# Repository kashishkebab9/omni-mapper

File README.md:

# omni-mapper

Omni-Wheeled Robot with custom PCB
All Mechanical Assemblies, PCBs, Firmware, and Software designed, architected and programmed by Kashish Garg

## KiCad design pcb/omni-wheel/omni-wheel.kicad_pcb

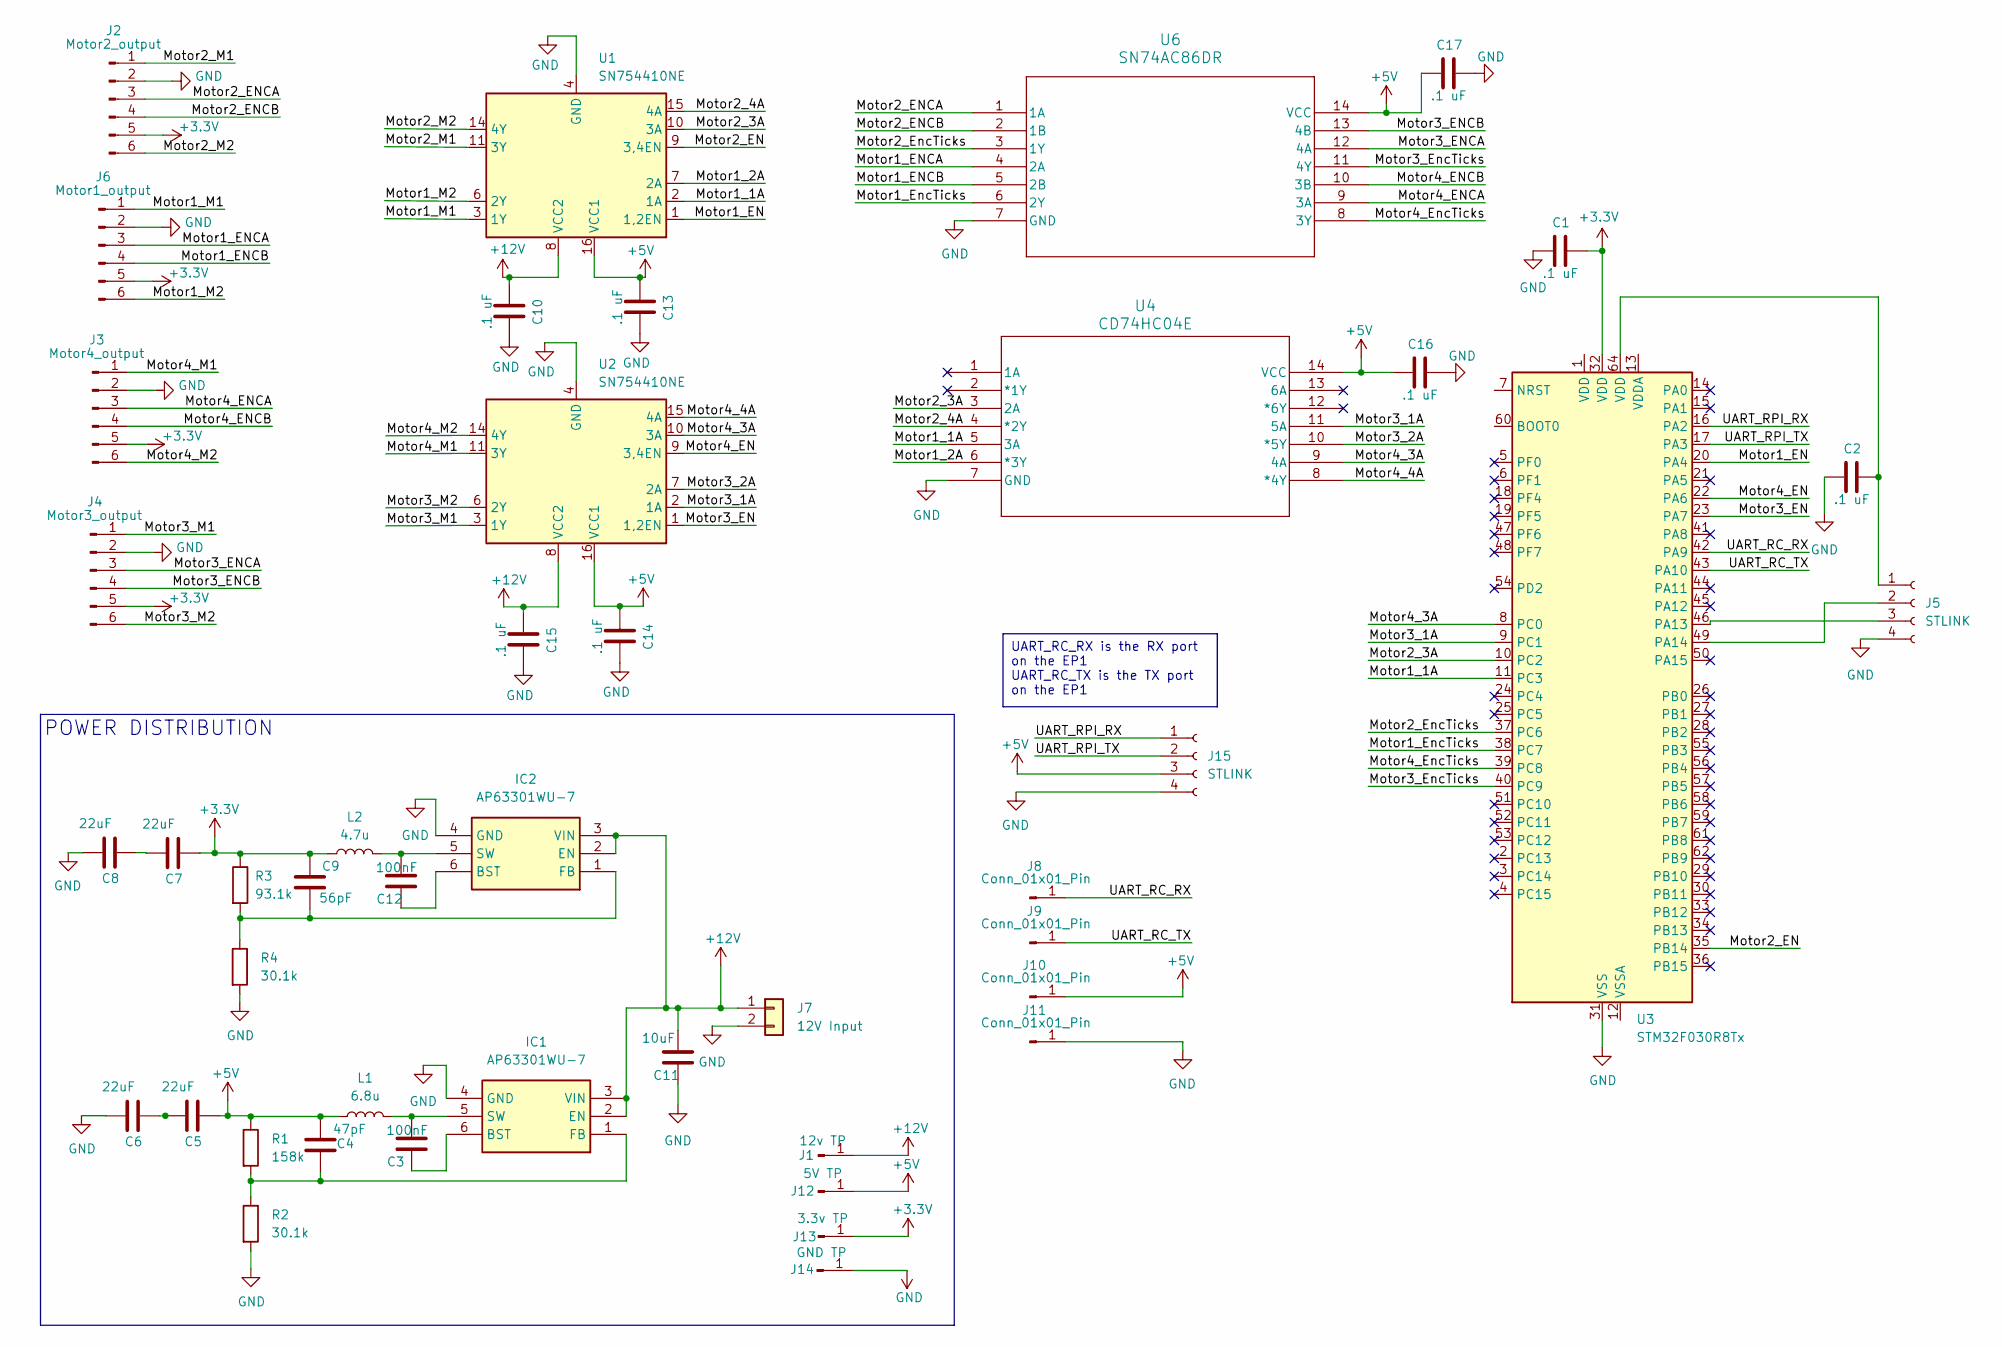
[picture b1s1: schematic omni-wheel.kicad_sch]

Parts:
C1, C2, C10, C13, C14, C15, C16, C17: .1 uF; C_0603_1608Metric; digikey# 311-1088-2-ND
C3, C12: 100nF; C_0603_1608Metric; digikey# 311-1088-2-ND
C4: 47pF; C_0603_1608Metric; digikey# 1276-1037-2-ND
C5, C6, C7, C8: 22uF; C_0603_1608Metric; digikey# 1276-1274-2-ND
C9: 56pF; C_0603_1608Metric; digikey# 1276-1197-2-ND
C11: 10uF; C_0603_1608Metric; digikey# 1276-1119-2-ND
IC1, IC2: AP63301WU-7; SOT95P280X100-6N; Manufacturer_Part_Number AP63301WU-7; digikey# 31-AP63301WU-7TR-ND
J1: 12v TP; TestPoint_THTPad_1.0x1.0mm_Drill0.5mm
J2: Motor2_output; JST_PH_B6B-PH-K_1x06_P2.00mm_Vertical
J3: Motor4_output; JST_PH_B6B-PH-K_1x06_P2.00mm_Vertical
J4: Motor3_output; JST_PH_B6B-PH-K_1x06_P2.00mm_Vertical
J5, J15: STLINK; PinHeader_1x04_P2.54mm_Vertical
J6: Motor1_output; JST_PH_B6B-PH-K_1x06_P2.00mm_Vertical
J7: 12V Input; AMASS_XT60PW-M_1x02_P7.20mm_Horizontal
J8, J9, J10, J11: Conn_01x01_Pin; TestPoint_THTPad_2.0x2.0mm_Drill1.0mm
J12: 5V TP; TestPoint_THTPad_1.0x1.0mm_Drill0.5mm
J13: 3.3v TP; TestPoint_THTPad_1.0x1.0mm_Drill0.5mm
J14: GND TP; TestPoint_THTPad_1.0x1.0mm_Drill0.5mm
L1: 6.8u; L_0603_1608Metric; digikey# 535-11606-2-ND
L2: 4.7u; L_0603_1608Metric; digikey# 535-11602-2-ND
R1: 158k; R_0603_1608Metric; digikey# 541-158KHTR-ND
R2, R4: 30.1k; R_0603_1608Metric; digikey# 311-30.1KHRTR-ND
R3: 93.1k; R_0603_1608Metric
U1, U2: SN754410NE; DIP-16_W7.62mm
U3: STM32F030R8Tx; LQFP-64_10x10mm_P0.5mm
U4: CD74HC04E; N14
U6: SN74AC86DR; D14

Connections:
+3.3V: C1.2, C7.2, C9.1, J2.5, J3.5, J4.5, J6.5, J13.1, L2.1, R3.1, U3.32 (VDD)
+5V: C4.1, C5.2, C13.1, C14.1, C16.1, C17.1, J10.1, J12.1, J15.3, L1.1, R1.1, U1.16 (VCC1), U2.16 (VCC1), U4.14 (VCC), U6.14 (VCC)
/Motor1_1A: U1.2 (1A), U3.11 (PC3), U4.5 (3A)
/Motor1_2A: U1.7 (2A), U4.6 (*3Y)
/Motor1_EN: U1.1 (1,2EN), U3.20 (PA4)
/Motor1_ENCA: J6.3, U6.4 (2A)
/Motor1_ENCB: J6.4, U6.5 (2B)
/Motor1_EncTicks: U3.38 (PC7), U6.6 (2Y)
/Motor1_M1: J6.1, U1.3 (1Y)
/Motor1_M2: J6.6, U1.6 (2Y)
/Motor2_3A: U1.10 (3A), U3.10 (PC2), U4.3 (2A)
/Motor2_4A: U1.15 (4A), U4.4 (*2Y)
/Motor2_EN: U1.9 (3,4EN), U3.35 (PB14)
/Motor2_ENCA: J2.3, U6.1 (1A)
/Motor2_ENCB: J2.4, U6.2 (1B)
/Motor2_EncTicks: U3.37 (PC6), U6.3 (1Y)
/Motor2_M1: J2.1, U1.11 (3Y)
/Motor2_M2: J2.6, U1.14 (4Y)
/Motor3_1A: U2.2 (1A), U3.9 (PC1), U4.11 (5A)
/Motor3_2A: U2.7 (2A), U4.10 (*5Y)
/Motor3_EN: U2.1 (1,2EN), U3.23 (PA7)
/Motor3_ENCA: J4.3, U6.12 (4A)
/Motor3_ENCB: J4.4, U6.13 (4B)
/Motor3_EncTicks: U3.40 (PC9), U6.11 (4Y)
/Motor3_M1: J4.1, U2.3 (1Y)
/Motor3_M2: J4.6, U2.6 (2Y)
/Motor4_3A: U2.10 (3A), U3.8 (PC0), U4.9 (4A)
/Motor4_4A: U2.15 (4A), U4.8 (*4Y)
/Motor4_EN: U2.9 (3,4EN), U3.22 (PA6)
/Motor4_ENCA: J3.3, U6.9 (3A)
/Motor4_ENCB: J3.4, U6.10 (3B)
/Motor4_EncTicks: U3.39 (PC8), U6.8 (3Y)
/Motor4_M1: J3.1, U2.11 (3Y)
/Motor4_M2: J3.6, U2.14 (4Y)
/UART_RC_RX: J8.1, U3.42 (PA9)
/UART_RC_TX: J9.1, U3.43 (PA10)
/UART_RPI_RX: J15.1, U3.16 (PA2)
/UART_RPI_TX: J15.2, U3.17 (PA3)
GND: C1.1, C2.1, C6.1, C8.1, C10.2, C11.2, C13.2, C14.2, C15.2, C16.2, C17.2, IC1.4 (GND), IC2.4 (GND), J2.2, J3.2, J4.2, J5.4, J6.2, J7.2, J11.1, J14.1, J15.4, R2.2, R4.2, U1.4 (GND), U1.5 (GND), U1.12 (GND), U1.13 (GND), U2.4 (GND), U2.5 (GND), U2.12 (GND), U2.13 (GND), U3.31 (VSS), U3.63 (VSS), U4.7 (GND), U6.7 (GND)
unnamed: C5.1, C6.2
unnamed: C7.1, C8.2
unnamed: C3.2, IC1.6 (BST)
unnamed: C4.2, IC1.1 (FB), R1.2, R2.1
unnamed: C3.1, IC1.5 (SW), L1.2
unnamed: C12.2, IC2.6 (BST)
unnamed: C9.2, IC2.1 (FB), R3.2, R4.1
unnamed: C12.1, IC2.5 (SW), L2.2
unnamed: C2.2, J5.1, U3.64 (VDD)
unnamed: J5.2, U3.49 (PA14)
unnamed: J5.3, U3.46 (PA13)

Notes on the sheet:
UART_RC_RX is the RX port on the EP1 UART_RC_TX is the TX port on the EP1
POWER DISTRIBUTION

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
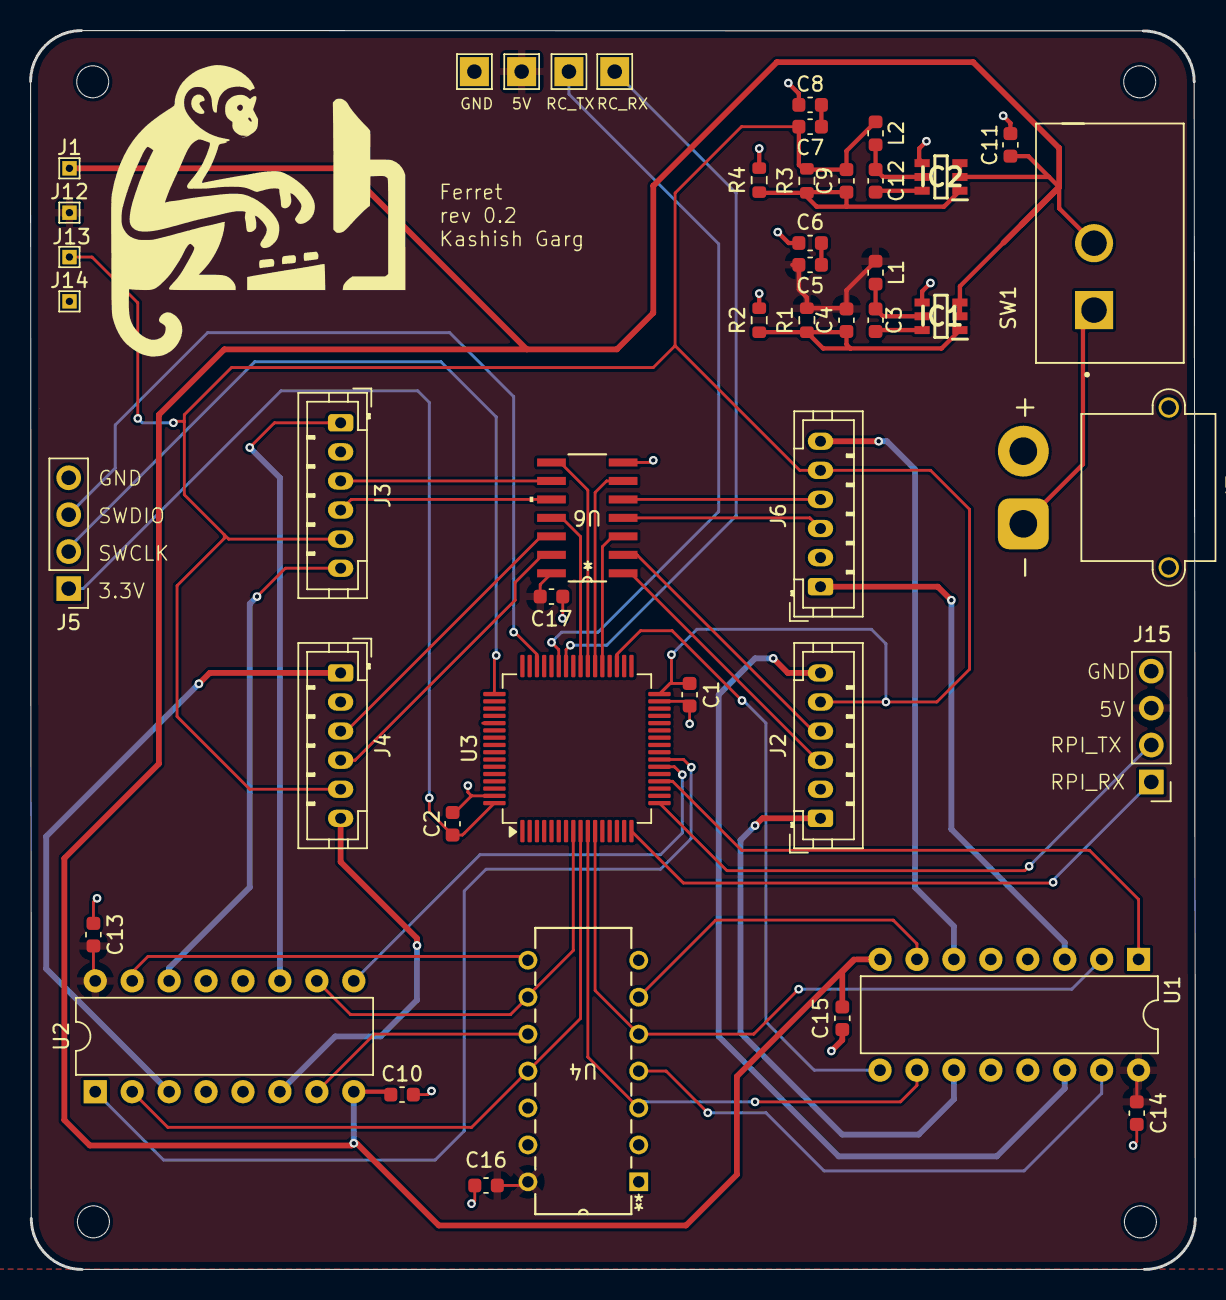
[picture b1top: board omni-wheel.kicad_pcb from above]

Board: 2 copper layers, 80.1 x 85.2 mm, 46 parts (0 on the bottom side), 52 nets.

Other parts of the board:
SW1: SW_SPST; SW_GF-123-0054

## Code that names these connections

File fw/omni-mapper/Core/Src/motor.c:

/*
 * Copyright (c) 2024 Kashish Garg
 *
 * Permission is hereby granted, free of charge, to any person obtaining a copy
 * of this software and associated documentation files (the "Software"), to deal
 * in the Software without restriction, including without limitation the rights
 * to use, copy, modify, merge, publish, distribute, sublicense, and/or sell
 * copies of the Software, and to permit persons to whom the Software is
 * furnished to do so, subject to the following conditions:
 *
 * The above copyright notice and this permission notice shall be included in all
 * copies or substantial portions of the Software.
 *
 * THE SOFTWARE IS PROVIDED "AS IS", WITHOUT WARRANTY OF ANY KIND, EXPRESS OR
 * IMPLIED, INCLUDING BUT NOT LIMITED TO THE WARRANTIES OF MERCHANTABILITY,
 * FITNESS FOR A PARTICULAR PURPOSE AND NONINFRINGEMENT. IN NO EVENT SHALL THE
 * AUTHORS OR COPYRIGHT HOLDERS BE LIABLE FOR ANY CLAIM, DAMAGES OR OTHER
 * LIABILITY, WHETHER IN AN ACTION OF CONTRACT, TORT OR OTHERWISE, ARISING FROM,
 * OUT OF OR IN CONNECTION WITH THE SOFTWARE OR THE USE OR OTHER DEALINGS IN THE
 * SOFTWARE.
 */

#include "motor.h"
#include "timer.h"
#include "gpio.h"
#include "stm32f0xx_hal.h"
#include <stdint.h>

// We will be using the SN7544 Dual H-Bridge Motor Driver
// The four pins for PWM I am thinking are:
// PA4  (Pin 20) -> Time14_CH1 AF4 :: Motor 1 EN (3,4EN)
// PB14 (Pin 36) -> Time15_CH1 AF0 :: Motor 2 EN (1,2EN)
// PA6  (Pin 22) -> Time16_CH1 AF5 :: Motor 3 EN (1,2EN)
// PA7  (Pin 23) -> Time17_CH1 AF5 :: Motor 4 EN (3,4EN)


void SetupMotorPwm(GPIO_TypeDef * GPIOx, uint8_t pwm_pin, uint8_t af){
  
  // TODO: Check if TIMx is NULL   
  
  TIM_TypeDef * TIMx = SetupTimer(GPIOx, pwm_pin, af);

  // Settings for 0% duty cycle, change CCR1 for the duty cycle/speed required
  TIMx->CCR1 = 21;
  TIMx->PSC = 8000;
  TIMx->ARR = 20;

  // Set CCMR1 as Output
  TIMx->CCMR1 &~ (1 << 0); 
  TIMx->CCMR1 &~ (1 << 1); 

  // Active Polarity High
  TIMx->CCER |= (1 << 1);

  // PWM Mode
  TIMx->CCMR1 |= (1 << 6);
  TIMx->CCMR1 |= (1 << 5);
  TIMx->CCMR1 &~ (1 << 4);

  // Enable Compare Channel 1
  TIMx->CCER |= (1 << 0);

  // Initialize all Registers
  TIMx->EGR |= (1 << 0);

  // Enable output
  TIMx->BDTR |= (1 << 15);

  // 8MHZ / 8000 = 1000 cts/second
  TIMx->CR1 |= (1 << 0);

}

void SetupMotorDir(GPIO_TypeDef * GPIOx, uint8_t dir_pin){
  
  SetupGpioOut(GPIOx, dir_pin);

  // test:
  SetGpioOutOn(GPIOx, dir_pin);

}


void SetupMotor(MotorHandle motor_handle) {

  SetupMotorPwm(motor_handle.GPIOx_pwm, motor_handle.pwm_pin, motor_handle.pwm_af);
  SetupMotorDir(motor_handle.GPIOx_dir, motor_handle.dir_pin);
  SetupMotorEnc(motor_handle.GPIOx_enc, motor_handle.enc_pin);

}

void SetMotorDutyCycle(MotorHandle motor_handle, uint8_t pwm) {
  // Input a percentage (0- 100)
  // TODO: Set ErrorHandler if pwm is out of bounds
  
  TIM_TypeDef *TIMx = get_timer_from_pin(motor_handle.GPIOx_pwm, motor_handle.pwm_pin, motor_handle.pwm_af);

  if (pwm == 0) {
    TIMx->CCR1 = 21;

  } else {

    // x / 100 = y / 20
    // 20x = 100y
    // .2x = y

    pwm /= (int)pwm/5;
    TIMx->CCR1 = pwm;

  }
}

void SetupMotorEnc(GPIO_TypeDef * GPIOx, uint8_t enc_pin){
  
  SetupGpioIn(GPIOx, enc_pin);

}

void SetMotorDirection(){
}

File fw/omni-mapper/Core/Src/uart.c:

/*
 * Copyright (c) 2024 Kashish Garg
 *
 * Permission is hereby granted, free of charge, to any person obtaining a copy
 * of this software and associated documentation files (the "Software"), to deal
 * in the Software without restriction, including without limitation the rights
 * to use, copy, modify, merge, publish, distribute, sublicense, and/or sell
 * copies of the Software, and to permit persons to whom the Software is
 * furnished to do so, subject to the following conditions:
 *
 * The above copyright notice and this permission notice shall be included in all
 * copies or substantial portions of the Software.
 *
 * THE SOFTWARE IS PROVIDED "AS IS", WITHOUT WARRANTY OF ANY KIND, EXPRESS OR
 * IMPLIED, INCLUDING BUT NOT LIMITED TO THE WARRANTIES OF MERCHANTABILITY,
 * FITNESS FOR A PARTICULAR PURPOSE AND NONINFRINGEMENT. IN NO EVENT SHALL THE
 * AUTHORS OR COPYRIGHT HOLDERS BE LIABLE FOR ANY CLAIM, DAMAGES OR OTHER
 * LIABILITY, WHETHER IN AN ACTION OF CONTRACT, TORT OR OTHERWISE, ARISING FROM,
 * OUT OF OR IN CONNECTION WITH THE SOFTWARE OR THE USE OR OTHER DEALINGS IN THE
 * SOFTWARE.
 */

#include "uart.h"
#include <stdint.h>
#include <string.h>
#include <stdio.h>

// There are only two UART peripherals that we can use on this mcu
// No need to map things, we can just have two functions to set up each of these
// PA9  (Pin 42) -> USART1_TX AF1 :: RC RX
// PA10 (Pin 43) -> USART1_RX AF1 :: RC TX
// PA2  (Pin 16) -> USART2_TX AF1 :: RaspberryPi RX
// PA3  (Pin 17) -> USART2_RX AF1 :: RaspberryPi TX

USART_TypeDef* SetupUartRc() {

  // All ports get enabled in main()
  // RCC->AHBENR |= RCC_AHBENR_GPIOAEN;
  
  /* 
   * Enable the USART1 Peripheral in RCC
   * Page 114 of 
   * https://www.newbiehack.com/Documents/STM32F030Reference.pdf
  */ 
  RCC->APB2ENR |= (1 << 14);

  /* 
   * Alternate Pin Mode
   * Page 137 of 
   * https://www.newbiehack.com/Documents/STM32F030Reference.pdf
   * and Page 34 of 
   * https://www.st.com/content/ccc/resource/technical/document/datasheet/a4/5d/0b/0e/87/c4/4d/71/DM00088500.pdf/files/DM00088500.pdf/jcr:content/translations/en.DM00088500.pdf
  */ 
  GPIOA->MODER |= (1 << 21);
  GPIOA->MODER &~ (1 << 20);
  GPIOA->MODER |= (1 << 19);
  GPIOA->MODER &~ (1 << 18);

  /* 
   * Actual Alternate Function Number (AF1) for both Pin 9 and 10
   * Page 142 of 
   * https://www.newbiehack.com/Documents/STM32F030Reference.pdf
  */ 
  GPIOA->AFR[1] &~ (1 << 7);
  GPIOA->AFR[1] &~ (1 << 6);
  GPIOA->AFR[1] &~ (1 << 5);
  GPIOA->AFR[1] |= (1 << 4);

  GPIOA->AFR[1] &~ (1 << 11);
  GPIOA->AFR[1] &~ (1 << 10);
  GPIOA->AFR[1] &~ (1 << 9);
  GPIOA->AFR[1] |= (1 << 8);

  /* 
   * Program the M0 and M1 Bit in the USART CR1
   * 00 for 8 bit word length
   * Disable USART while we configure          
   * Page 623 of 
   * https://www.newbiehack.com/Documents/STM32F030Reference.pdf
  */ 

  USART1->CR1 = 0x00000000;
  USART1->CR1 &~ (1 << 12);
  USART1->CR1 &~ (1 << 28);
  USART1->CR1 &~ (1 << 0);

  /* 
   * BRR
   * Our Clock rate is 8MHz
   * We want to oversample by 16. Meaning the RX line will sample 16x more the baudrate
   *Baud = 115200
   * Clock = 8,000,000
   * USART_DIV = 8,000,000/115200
   * USART_DIV = 69.4 => 69
   * Page 631 of 
   * https://www.newbiehack.com/Documents/STM32F030Reference.pdf
  */ 

  uint32_t reg = USART1->BRR;
  reg |= 69;
  USART1->BRR = reg;

  /* 
   * Program the Number of Stop Bits in USART CR2
   * minicom uses 1 stop bit by default
   * Page 142 of 
   * https://www.newbiehack.com/Documents/STM32F030Reference.pdf
  */ 

  USART1->CR2 &~ (1 << 13);
  USART1->CR2 &~ (1 << 12);

  /* 
   * Enable the USART by writing the UE bit in USART_CR1 register to 1
   * minicom uses 1 stop bit by default
   * Page 623 of 
   * https://www.newbiehack.com/Documents/STM32F030Reference.pdf
  */ 
  USART1->CR1 |= (1<<0);

  return USART1;
}

USART_TypeDef* SetupUartRpi() {
  // All ports get enabled in main()
  // RCC->AHBENR |= RCC_AHBENR_GPIOAEN;
  
  /* 
   * Enable the USART1 Peripheral in RCC
   * Page 114 of 
   * https://www.newbiehack.com/Documents/STM32F030Reference.pdf
  */ 
  RCC->APB1ENR |= (1 << 17);

  /* 
   * Alternate Pin Mode
   * Page 137 of 
   * https://www.newbiehack.com/Documents/STM32F030Reference.pdf
   * and Page 34 of 
   * https://www.st.com/content/ccc/resource/technical/document/datasheet/a4/5d/0b/0e/87/c4/4d/71/DM00088500.pdf/files/DM00088500.pdf/jcr:content/translations/en.DM00088500.pdf
  */ 
  GPIOA->MODER |= (1 << 7);
  GPIOA->MODER &~ (1 << 6);
  GPIOA->MODER |= (1 << 5);
  GPIOA->MODER &~ (1 << 4);

  /* 
   * Actual Alternate Function Number (AF1) for both Pin 9 and 10
   * Page 142 of 
   * https://www.newbiehack.com/Documents/STM32F030Reference.pdf
  */ 
  GPIOA->AFR[0] &~ (1 << 11);
  GPIOA->AFR[0] &~ (1 << 10);
  GPIOA->AFR[0] &~ (1 << 9);
  GPIOA->AFR[0] |= (1 << 8);

  GPIOA->AFR[0] &~ (1 << 15);
  GPIOA->AFR[0] &~ (1 << 14);
  GPIOA->AFR[0] &~ (1 << 13);
  GPIOA->AFR[0] |= (1 << 12);

  /* 
   * Program the M0 and M1 Bit in the USART CR1
   * 00 for 8 bit word length
   * Disable USART while we configure          
   * Page 623 of 
   * https://www.newbiehack.com/Documents/STM32F030Reference.pdf
  */ 

  USART2->CR1 = 0x00000000;
  USART2->CR1 &~ (1 << 12);
  USART2->CR1 &~ (1 << 28);
  USART2->CR1 &~ (1 << 0);

  /* 
   * BRR
   * Our Clock rate is 8MHz
   * We want to oversample by 16. Meaning the RX line will sample 16x more the baudrate
   *Baud = 115200
   * Clock = 8,000,000
   * USART_DIV = 8,000,000/115200
   * USART_DIV = 69.4 => 69
   * Page 631 of 
   * https://www.newbiehack.com/Documents/STM32F030Reference.pdf
  */ 

  uint32_t reg = USART2->BRR;
  reg |= 69;
  USART2->BRR = reg;

  /* 
   * Program the Number of Stop Bits in USART CR2
   * minicom uses 1 stop bit by default
   * Page 142 of 
   * https://www.newbiehack.com/Documents/STM32F030Reference.pdf
  */ 

  USART2->CR2 &~ (1 << 13);
  USART2->CR2 &~ (1 << 12);

  /* 
   * Enable the USART by writing the UE bit in USART_CR1 register to 1
   * minicom uses 1 stop bit by default
   * Page 623 of 
   * https://www.newbiehack.com/Documents/STM32F030Reference.pdf
  */ 
  USART2->CR1 |= (1<<0);
  return USART2;
}

void ReceiveUart(USART_TypeDef* USARTx) {

}

void TransmitUartString(USART_TypeDef* USARTx, char* string_tx) {
  USARTx->CR2 &~ USART_CR2_STOP_0;
  USARTx->CR2 &~ USART_CR2_STOP_1;

  // Enable the USART by writing the UE bit in USART_CR1 register to 1
  USARTx->CR1 |= (1<<0);

  // Set the TE bit in USART_CR1 to send an idle frame as first transmission.
  USARTx->CR1 |= (1<<3);
  USARTx->CR3 = 0x00;

  int send = 0;

  while(1) {
	  if (send == (int)strlen(string_tx)){
      return;
	  }
	  USARTx->TDR = string_tx[send++];
	  while(!(USARTx->ISR & 1<<6));
  }

}

void TransmitUartFloat(USART_TypeDef* USARTx, float float_tx) {
  char string_buffer[50];
  sprintf(string_buffer, "%.2f", float_tx);
  TransmitUartString(USARTx, string_buffer);

}

void TransmitUartInt(USART_TypeDef* USARTx, int int_tx){
  
}

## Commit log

2022-12-08 cleaner translation calc
2022-12-08 kd tree steps written out
2022-12-08 Work on KD Tree when I get home
2022-12-09 KD Tree implementation from OpenAI ChatGPT
2022-12-09 Building kdtree to understand data structure more
2022-12-09 writing out structure for kdtree
2022-12-09 More NN work
2022-12-12 initial kdtree nearest neighbor draft- NEEDS TESTING
2022-12-12 working kd tree class in test/
2022-12-12 working kdtree, working on nn, in progress
2022-12-13 I think nearest neighbor is working
2022-12-13 Working kdtree in include dir
2022-12-13 cleaned up messages for info/debugging
2022-12-14 some notes on how to do icp solver
2022-12-17 removed build/log files and added recursive unwinding to kd tree nn
2022-12-17 hopefully logs/build is cleaned now, save point before implementing std::pair data structure in kdtree
2022-12-17 cleaned up averages calc and added std::pair output from kdtree
2022-12-17 working prime vector formulation
2022-12-17 W_SVD Formulation, NEEDS TESTING
2022-12-17 SVD seems to compile, needs more testing though
2022-12-17 I think working SVD and rotation extractor
2022-12-20 save point, before actual recursive testing
2022-12-20 added equation for translation, still need to loop
2022-12-22 Added initial transformation calculation to start looping
2022-12-22 cleaned up comments throughout icp node
2022-12-22 added centroid method
2022-12-22 issues with iterating for the solution
2022-12-24 clean build save spot 12_24_22
2022-12-24 rotation seems to be working, translation is borked
2022-12-24 nvm, nothing works, smh
2022-12-26 save point, I need to do some data wrangling to throw away (or just not process) any zero-data points, as that throws off centroid and variance calculations
2022-12-26 still not working, need to figure out the issue with the error calc in while loop
2022-12-28 added matlab script for support
2022-12-28 got nearest neighbor working in matlab
2022-12-28 working transformation matrix, just need to animate transform now
2022-12-28 working icp algorithm within matlab, need to translate this effort into a test in c++
2022-12-28 restarted icp_node dev, working transformation, onto debugging knn tree search
2022-12-28 added notes on what is left to work on
2022-12-29 added kdtree to ensure kdtree function is working as expected, need to write out test still, wrote some pseudocode for error optimization in icp_retry too
2022-12-30 kdtree_test proves our kdtree algorithm is solid
2022-12-30 save point, error supervisor is not working
2022-12-30 I'm tired so i am commiting and working on this later
2022-12-30 I think it is working now? need to validate in matlab
2023-01-03 fixed minor bug with centroid calculation, need to work more on validating ICP
2023-01-03 convinced that our transformation solver is the issue
2023-04-03 cleaned up node, added centroid markers
2023-04-04 added node to convert laserscan into pointcloud
2023-04-04 now using pointcloud instead of scan
2023-04-06 added visualizations, logic within transformation loop seems to be concerning
2023-04-07 Working ICP Point to Point!
2023-04-07 ICP works, but not well
2023-04-09 Trying to visualize tf, but quaternion is invalid, apparently
2023-04-09 Added Quaternion check
2023-06-13 Added ekf
2023-06-19 Working Simulated encoder
2023-06-19 Cleaned up useless files
2023-06-19 added encoder publishing
2023-06-19 Encoder odometry looking good
2023-06-19 Working pose estimates from encoder readings, onto motion model!
2023-06-19 Wrong equation, updated
2023-06-20 Fixed issue with sim enc, need to add gaussian noise now
2024-10-07 cleaned up repo and added inital commit for the pcb, onto gcc cleanup for fw on stm32
2024-10-07 more clean up
2024-10-09 Started Make file dev, need to port to stm32_sphere after a better understanding
2024-10-17 Working stm32 compilation
2024-10-18 Working on Circuit design, got major components down schematic
2024-10-18 fixed small issue
2024-10-19 added motor.c
2024-10-19 added timer.c, onto timer config
2024-10-20 Clarified driver architecture, added to makefile
2024-10-21 Forgot AF register, struggling with hard fault
2024-10-21 Working pwm and timers.c
2024-10-21 added gitignore
2024-10-21 update gitignore
2024-10-21 deleted older gi
2024-10-21 Saved all relevant files
2024-10-21 Motor.c abstraction working beautifully
2024-10-21 motor abstraction not working beautifully :(
2024-10-21 Issue was with RCC, not motor abstraction
2024-10-21 RCC config within timer.c now
2024-10-21 GPIO implementation, need to test
2024-10-22 GPIO implementation Tested, seems to work!
2024-10-22 Working motor config, want to make custom data type
2024-10-22 MotorHandle implemented
2024-10-22 PCB additions
2024-10-25 PCB save
2024-10-25 metadata cleanup
2024-11-05 pcb update for home
2024-11-15 power distribution done, lay up is next
2024-11-16 routing almost done, need to logic pins next
2024-11-21 save before architecture change
2024-11-23 first pcb revision done
2024-11-23 Silkscreen added, just need to add 4-pin jumper, then release!
2024-11-24 Added rc uart connections, onto RPI
2024-11-24 Ferret Board rev 0.1 Release
2024-11-24 removed unneccessary zips folder
2024-11-24 cleaned up motor.c and changed motor 1 and 2 assignemnt in main
2024-11-24 added xt connector step
2024-11-24 First attempt for RC UART, needs testing
2024-11-24 Added MIT License
2024-11-25 Got UART Debugging working
2024-11-25 Got both uart peripherals working
2024-11-25 Got duty cycle setting done, needs testing
2025-01-04 saving changes made to fw
2025-01-04 Added power test points to pcb, going to change xt size and add toggle switch next
2025-01-04 Added smaller xt connector and power switch
2025-01-04 forgot to save schema
2025-01-04 Added smaller xt connector and power switch
    forgot to save schema
2025-01-05 purchased this iteration of the board
